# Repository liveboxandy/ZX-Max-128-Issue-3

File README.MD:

ZX Max 128 Issue 3.

This Kicad project has only been done so as to allow for a proper ibom that includes tracks and vias
to be created to make assembling easier.
A lot of work was done in order to ensure that the footprints were located as close as possible to 
those in the original as well tying to follow the existing track and via locations. Some of the
footprints that were downloaded from Digikey based on the parts in the official BOM do not fit 
exactly in their locations on the board. C15 is one example, I had to modify it's footprint to fit
the pad dimensions. Some other capacitors also do not fit correctly but appear to be close enough.

As such, although I have tried to be as accurate as possible I would NOT use these gerbers to have a
pcb manufactured without having another set of eyes checking that the schematic that I have produced
is correct to that produced by DonSuperfo and that the pcb data from Kicad reports no major errors 
with regards to copper tracing and via positions.

The KiCAD schematics 'should' be correct but nothing should be assumed as correct without checking with the original schematic and PCB layout. Although I have followed the original track and via layout further checking should be done before using these files to order a pcb with. Currently I would still order the pcb from PCBWay using the link from https://github.com/DonSuperfo/ZX-Max-128

Note that any part number for any device used in this project might not be the correct one from the original BOM as supplied from PCBWay as I had to change some parts to get a footprint that would fit in the space on the original pcb with the correct pin spacing. This required selecting a different part number or vendor. This applies mainly to capacitors. Some other parts are no longer available under that number from Digikey.

As always, measure twice and order one.

Use at your own risk.

For the jumpers/connectors on the board,

J1/J1A1 8 Way Keyboard Connector

J2/J2A1 5 Way Keyboard Connector

J3 Zx Expansion Connector

J4 DC Input can be any polarity. 

J5 Video is a TRRS, Tip-Video,RR-Left/Right, Screen-Ground.

J6 Ear/Mic. Wired as per ZX Spectrum 128K +3. TRS. Tip-Mic, Ring-Ear, Screen-Ground.

J7 Not Used

J8 SCART, mates with a Sega megadrive cable for SCART.

J9 Not Used

J10 EEPROM/EPROM selection, EEPROM 2-4/1-3, UVEPROM 2-1/4-3.

J11 Speaker On/Off

J12 Not Used

J13 Not Used

J14 JTAG for the EPM7128 wired as standard to an Altera device.

J15 Not Used

J16 Disable DivMMC, close = enable DivMMC, open = disable DivMMC or need to update program on U17

SW1 RESET

From information on the original website,

In order to make ACB output more balanced I would recommend following the -4.5 dB panning law rule and make these updates:

R54, R55 = 470 Ohm
R51, R52 = 560 Ohm
R50, R53 = 330 Ohm

The ratio of 560 / 330 = 1.6969 is a close approximation of 1 / 10^(-4.5 / 20) = 1.6788. 
Also the resulting equivalent resistance is around 1000 Ohm which leads to less distortion on AY outputs.

mismatch between the value on the scheme and in the BOM for part R32 (INT)
on scheme it is 470R but in BOM 10k.
it looks like in BOM incorrect value.

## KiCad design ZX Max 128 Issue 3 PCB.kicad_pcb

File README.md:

# ZX-Max-128-Issue-3
KiCAD created files for the ZX Max 128 Issue 3 designed by DonSuperfo

This Kicad project has only been done so as to allow for a proper ibom that includes tracks and vias
to be created.
A lot of work was done in order to ensure that the footprints were located as close as possible to 
those in the original as well tying to follow the existing track and via locations. Some of the
footprints that were downloaded from Digikey based on the parts in the official BOM do not fit 
exactly in their locations on the board. C15 is one example, I had to modify it's footprint to fit
the pad dimensions. Some other capacitors also do not fit correctly but appear to be close enough.

As such, although I have tried to be as accurate as possible I would NOT use these gerbers to have a
pcb manufactured without having another set of eyes checking that the schematic that I have produced
is correct to that produced by DonSuperfo and that the pcb data from Kicad reports no major errors 
with regards to copper tracing and via positions.

For the jumpers/connectors on the board,

J1 8 Way Keyboard Connector
J2 5 Way Keyboard Connector
J3 Zx Expansion Connector
J4 DC Input can be any polarity. 
J5 Video is a TRRS, Tip-Video,RR-Left/Right, Screen-Ground.
J6 Ear/Mic. Wired as per ZX Spectrum 128K +3. TRS. Tip-Mic, Ring-Ear, Screen-Ground.
J7 Not Used
J8 SCART, mates with a Sega megadrive cable for SCART.
J9 Not Used
J10 EPROM/EEPROM selection,
J11 Speaker On/Off
J12 Not Used
J13 Not Used
J14 JTAG for the EPM7128 wired as standard to an Altera device.
J15 Not Used
J16 Disable DivMMC, close = enable DivMMC, open = disable DivMMC or need to update program on U17
SW1 RESET

From information on the original website,

In order to make ACB output more balanced I would recommend following the -4.5 dB panning law rule and make these updates:

R54, R55 = 470 Ohm
R51, R52 = 560 Ohm
R50, R53 = 330 Ohm

The ratio of 560 / 330 = 1.6969 is a close approximation of 1 / 10^(-4.5 / 20) = 1.6788. 
Also the resulting equivalent resistance is around 1000 Ohm which leads to less distortion on AY outputs.

mismatch between the value on the scheme and in the BOM for part R32 (INT)
on scheme it is 470R but in BOM 10k.
it looks like in BOM incorrect value.

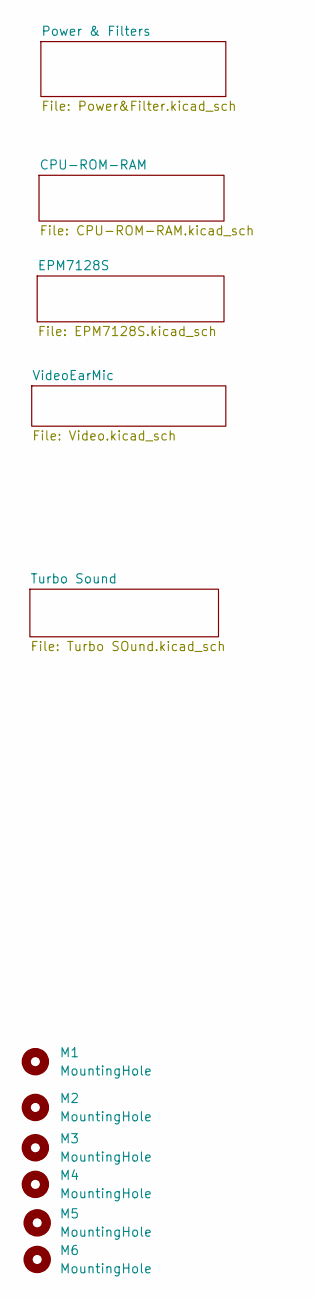
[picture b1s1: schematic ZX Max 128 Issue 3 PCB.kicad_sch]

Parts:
M1, M2, M3, M4, M5, M6: MountingHole; MountingHole_3.2mm_M3_DIN965

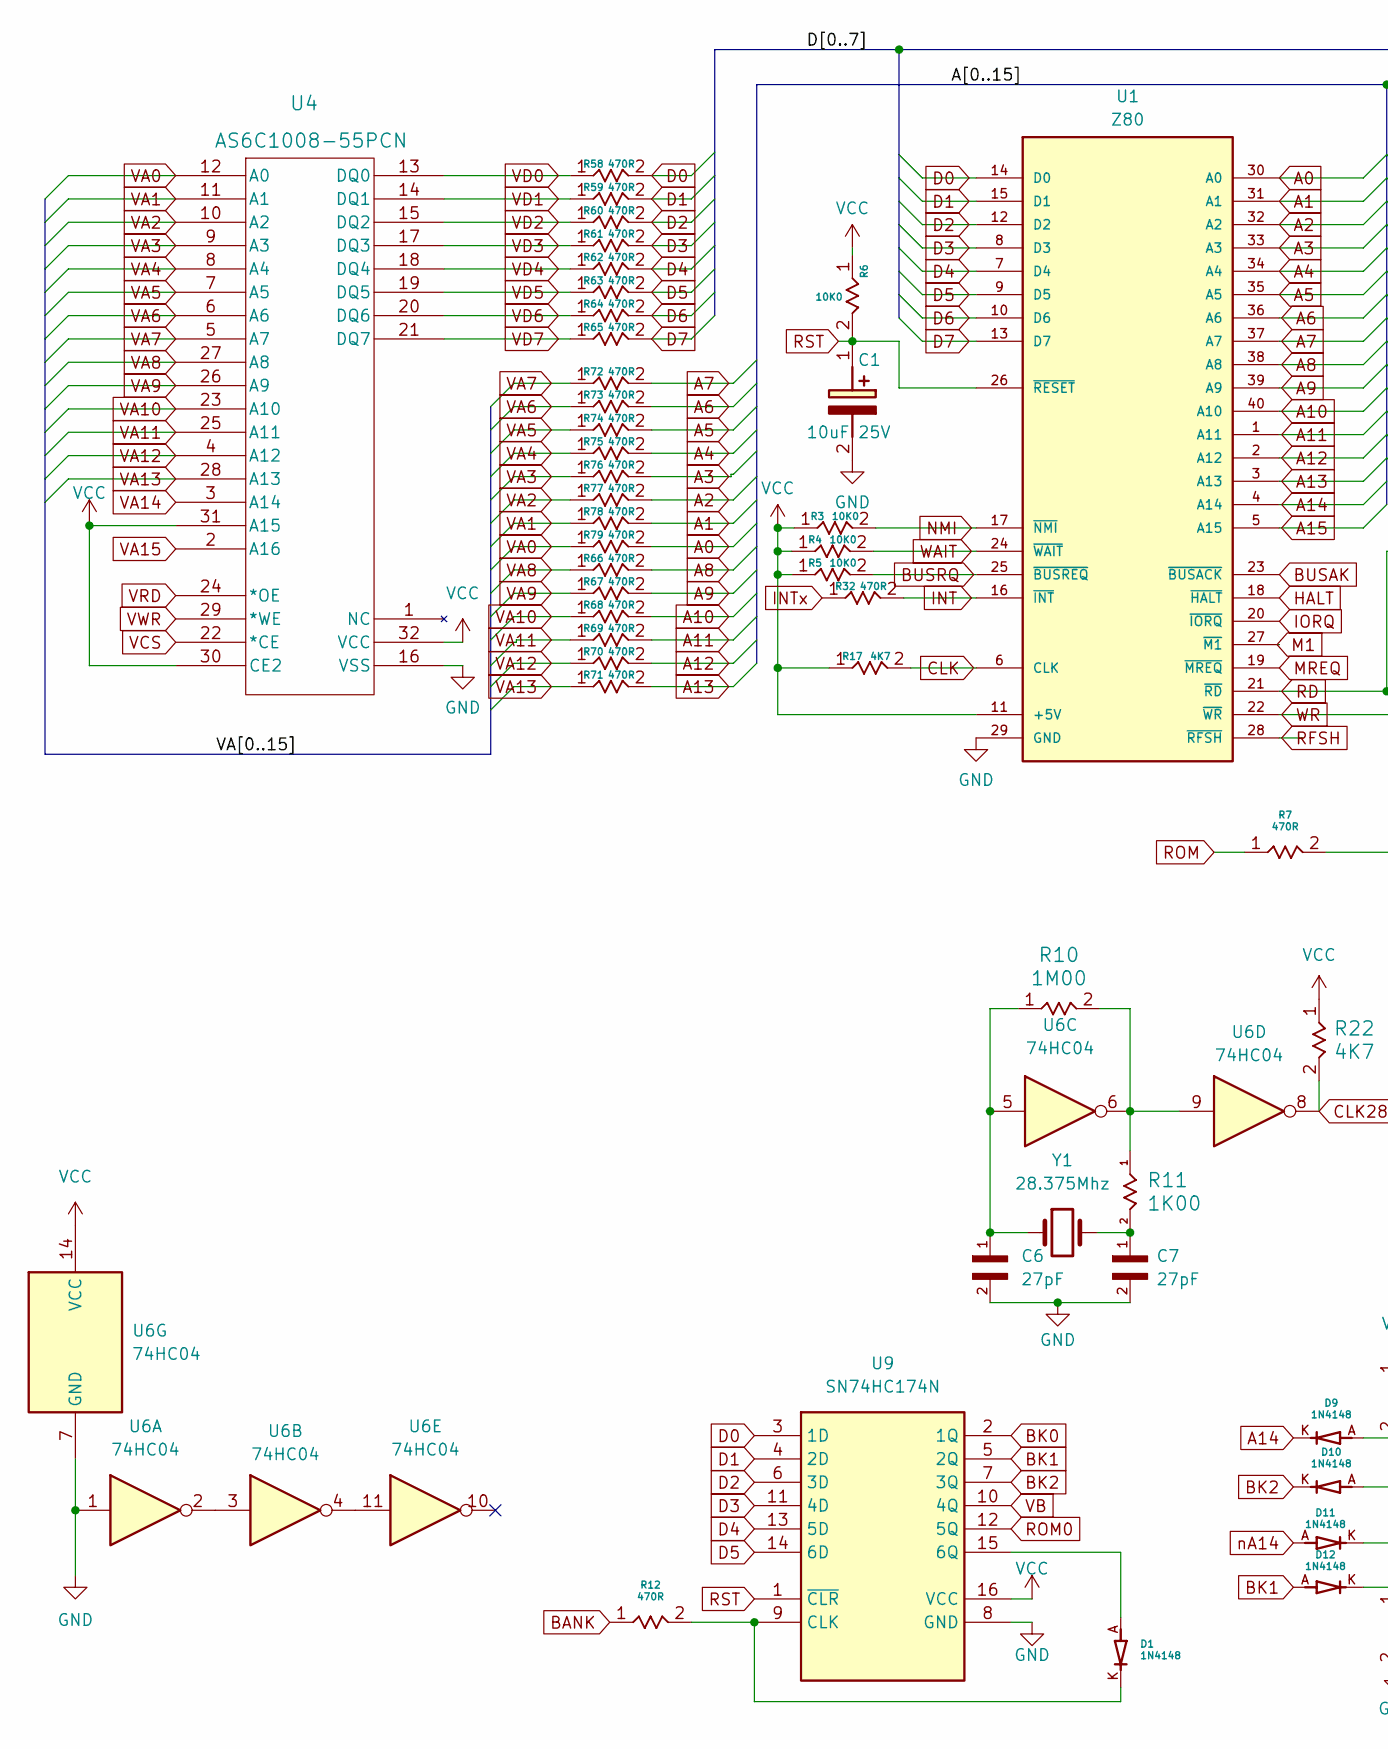
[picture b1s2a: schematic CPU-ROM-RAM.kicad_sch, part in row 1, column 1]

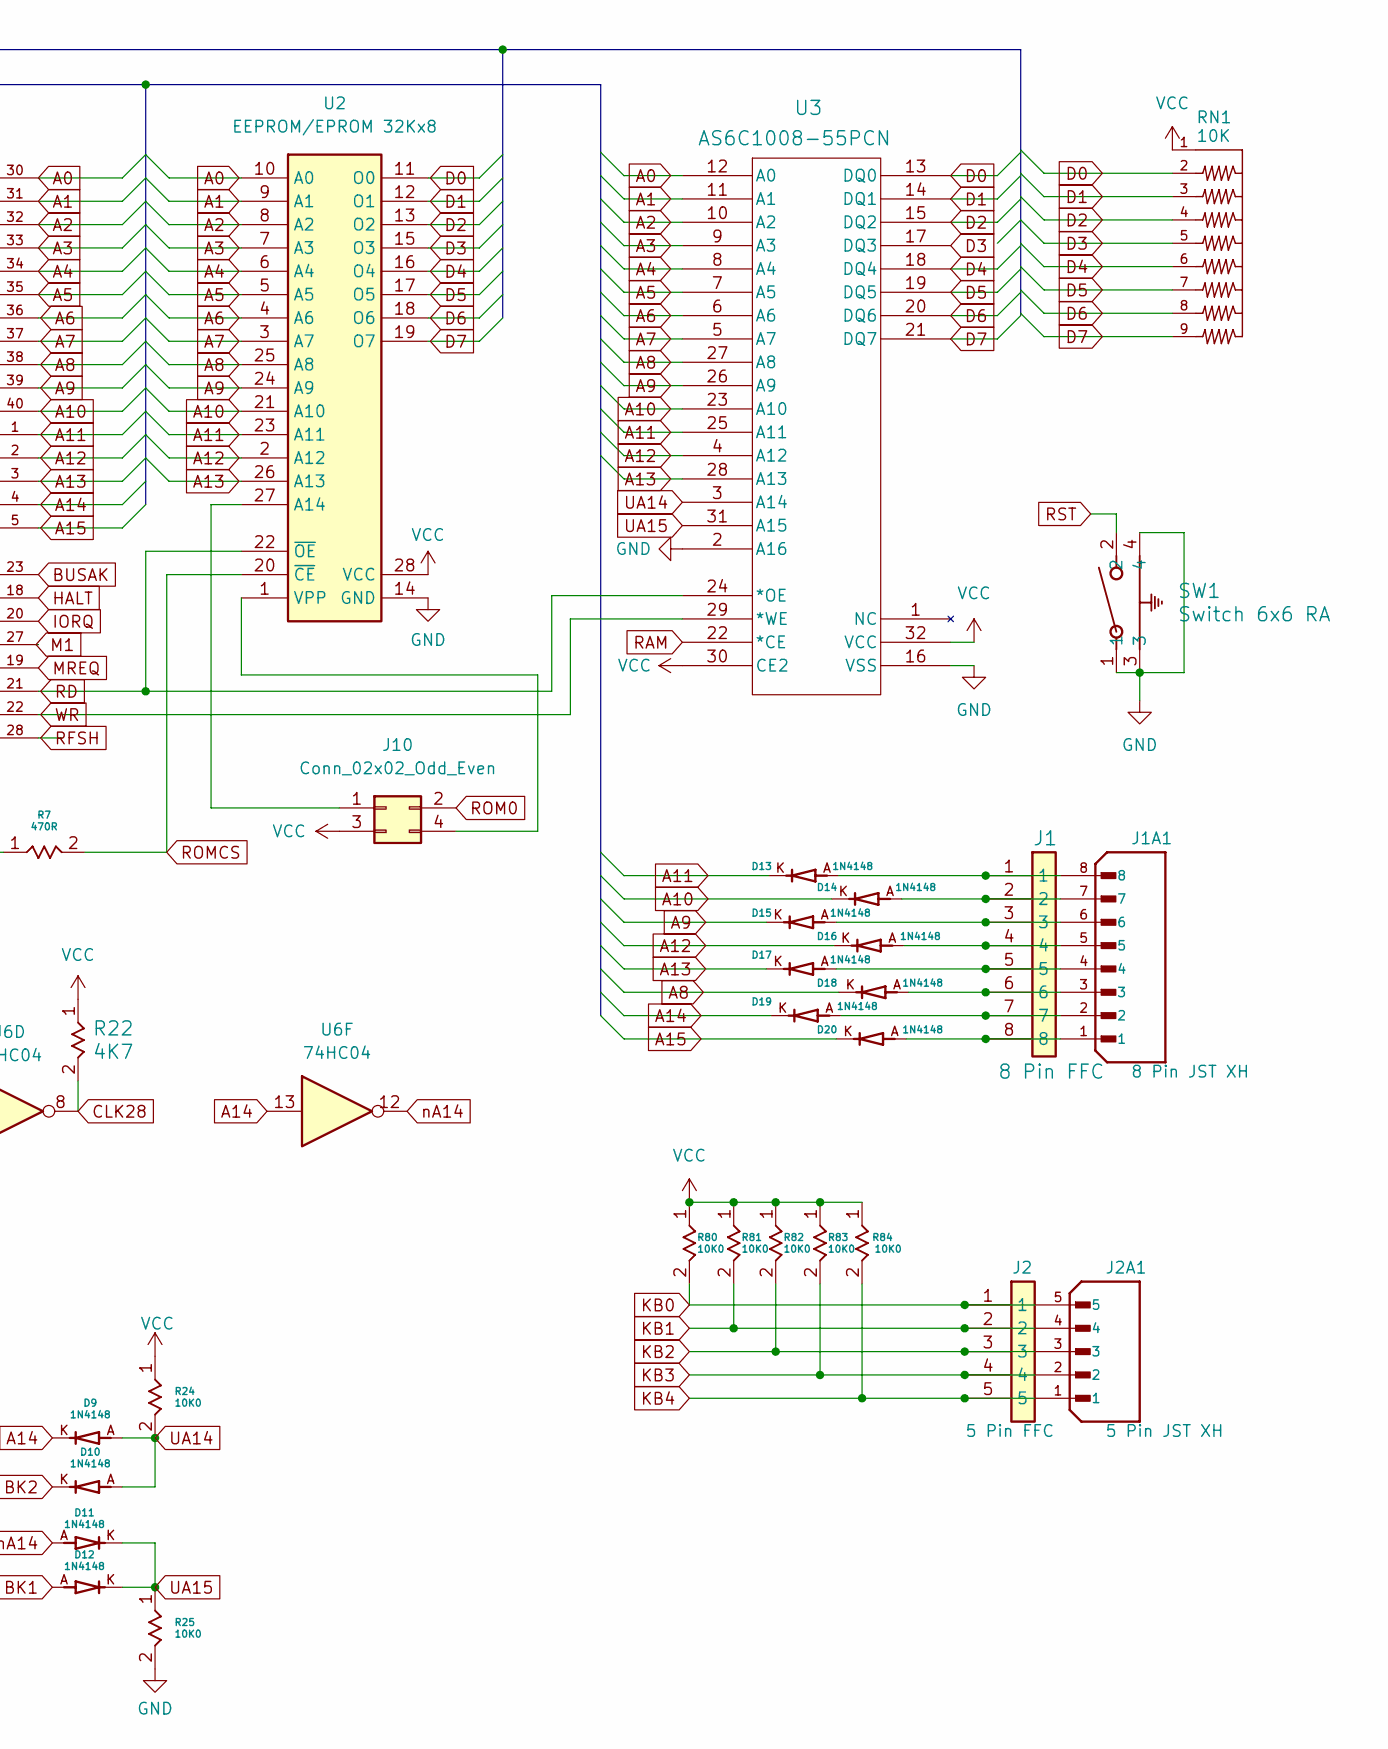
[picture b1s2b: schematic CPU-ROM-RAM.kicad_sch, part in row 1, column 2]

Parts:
C1: 10uF 25V; CAPPRD200W50D500H1100; Mouser Part Number 667-ECA-1EM100B
C6, C7: 27pF; CAPRB250W50L400T250H550; PARTREV 20200310
D1, D9, D10, D11, D12, D13, D14, D15, D16, D17, D18, D19, D20: 1N4148; DIOAD753W49L380D172B; PARTREV 5
J1: 8 Pin FFC; 55203155
J1A1: 8 Pin JST XH; JST_B8B-XH-A_LF__SN_; PARTREV 7/4/21
J2: 5 Pin FFC; 55203155; Mouser Part Number 571-5-520315-5
J2A1: 5 Pin JST XH; JST_B5B-XH-A_LF__SN_; PARTREV 7/4/21
J10: Conn_02x02_Odd_Even; PinHeader_2x02_P2.54mm_Vertical
R3, R4, R5, R6, R24, R25, R80, R81, R82, R83, R84: 10K0; STA_CF14_STP
R7, R12, R32, R58, R59, R60, R61, R62, R63, R64, R65, R66, R67, R68, R69, R70, R71, R72, R73, R74, R75, R76, R77, R78, R79: 470R; STA_CF14_STP
R10: 1M00; STA_CF14_STP
R11: 1K00; STA_CF14_STP
R17, R22: 4K7; STA_CF14_STP
RN1: 10K; SIP249W50P254L2281H508Q9; PARTREV 10/1/20
SW1: Switch 6x6 RA; SW2_1825027-G_TEC
U1: Z80; Z80_Socket
U2: EEPROM/EPROM 32Kx8; DIP1556W56P254L3702H483Q28N; Mouser Part Number 556-AT27C256R-45PU
U3: AS6C1008-55PCN; U3
U4: AS6C1008-55PCN; PDIP-32_MIL600_ALL
U6: 74HC04; DIP794W53P254L1930H508Q14N
U9: SN74HC174N; DIP794W53P254L1930H508Q16N; Mouser Part Number 595-SN74HC174N
Y1: 28.375Mhz; Crystal_HC49-4H_Vertical

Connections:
A0: R79.2, U1.30 (A0), U2.10 (A0), U3.12 (A0); also elsewhere on the board
A1: R78.2, U1.31 (A1), U2.9 (A1), U3.11 (A1); also elsewhere on the board
A2: R77.2, U1.32 (A2), U2.8 (A2), U3.10 (A2); also elsewhere on the board
A3: R76.2, U1.33 (A3), U2.7 (A3), U3.9 (A3); also elsewhere on the board
A4: R75.2, U1.34 (A4), U2.6 (A4), U3.8 (A4); also elsewhere on the board
A5: R74.2, U1.35 (A5), U2.5 (A5), U3.7 (A5); also elsewhere on the board
A6: R73.2, U1.36 (A6), U2.4 (A6), U3.6 (A6); also elsewhere on the board
A7: R72.2, U1.37 (A7), U2.3 (A7), U3.5 (A7); also elsewhere on the board
A8: D18.K, R66.2, U1.38 (A8), U2.25 (A8), U3.27 (A8); also elsewhere on the board
A9: D15.K, R67.2, U1.39 (A9), U2.24 (A9), U3.26 (A9); also elsewhere on the board
A10: D14.K, R68.2, U1.40 (A10), U2.21 (A10), U3.23 (A10); also elsewhere on the board
A11: D13.K, R69.2, U1.1 (A11), U2.23 (A11), U3.25 (A11); also elsewhere on the board
A12: D16.K, R70.2, U1.2 (A12), U2.2 (A12), U3.4 (A12); also elsewhere on the board
A13: D17.K, R71.2, U1.3 (A13), U2.26 (A13), U3.28 (A13); also elsewhere on the board
A14: D9.K, D19.K, U1.4 (A14), U6.13; also elsewhere on the board
A15: D20.K, U1.5 (A15); also elsewhere on the board
BANK: R12.1; also elsewhere on the board
BK0: U9.2 (1Q); also elsewhere on the board
BK1: D12.A, U9.5 (2Q); also elsewhere on the board
BK2: D10.K, U9.7 (3Q); also elsewhere on the board
BUSAK: U1.23 (~BUSACK); also elsewhere on the board
BUSRQ: R5.2, U1.25 (~BUSREQ); also elsewhere on the board
CLK: R17.2, U1.6 (CLK); also elsewhere on the board
CLK28: R22.2, U6.8; also elsewhere on the board
D0: R58.2, RN1.2, U1.14 (D0), U2.11 (O0), U3.13 (DQ0), U9.3 (1D); also elsewhere on the board
D1: R59.2, RN1.3, U1.15 (D1), U2.12 (O1), U3.14 (DQ1), U9.4 (2D); also elsewhere on the board
D2: R60.2, RN1.4, U1.12 (D2), U2.13 (O2), U3.15 (DQ2), U9.6 (3D); also elsewhere on the board
D3: R61.2, RN1.5, U1.8 (D3), U2.15 (O3), U3.17 (DQ3), U9.11 (4D); also elsewhere on the board
D4: R62.2, RN1.6, U1.7 (D4), U2.16 (O4), U3.18 (DQ4), U9.13 (5D); also elsewhere on the board
D5: R63.2, RN1.7, U1.9 (D5), U2.17 (O5), U3.19 (DQ5), U9.14 (6D); also elsewhere on the board
D6: R64.2, RN1.8, U1.10 (D6), U2.18 (O6), U3.20 (DQ6); also elsewhere on the board
D7: R65.2, RN1.9, U1.13 (D7), U2.19 (O7), U3.21 (DQ7); also elsewhere on the board
GND: C1.2 (-), C6.2, C7.2, R25.2, SW1.1, SW1.3, SW1.4, U1.29 (GND), U2.14 (GND), U3.2 (A16), U3.16 (VSS), U4.16 (VSS), U6.1, U6.7 (GND), U9.8 (GND); also elsewhere on the board
HALT: U1.18 (~HALT); also elsewhere on the board
INT: R32.2, U1.16 (~INT); also elsewhere on the board
INTx: R32.1; also elsewhere on the board
IORQ: U1.20 (~IORQ); also elsewhere on the board
KB0: J2.1, J2A1.5, R80.2; also elsewhere on the board
KB1: J2.2, J2A1.4, R81.2; also elsewhere on the board
KB2: J2.3, J2A1.3, R82.2; also elsewhere on the board
KB3: J2.4, J2A1.2, R83.2; also elsewhere on the board
KB4: J2.5, J2A1.1, R84.2; also elsewhere on the board
M1: U1.27 (~M1); also elsewhere on the board
MREQ: U1.19 (~MREQ); also elsewhere on the board
NMI: R3.2, U1.17 (~NMI); also elsewhere on the board
unnamed: C6.1, R10.1, U6.5, Y1.1
unnamed: C7.1, R11.2, Y1.2
unnamed: D13.A, J1.1, J1A1.8
unnamed: D14.A, J1.2, J1A1.7
unnamed: D15.A, J1.3, J1A1.6
unnamed: D16.A, J1.4, J1A1.5
unnamed: D17.A, J1.5, J1A1.4
unnamed: D18.A, J1.6, J1A1.3
unnamed: D19.A, J1.7, J1A1.2
unnamed: D20.A, J1.8, J1A1.1
unnamed: J10.1, U2.27 (A14)
unnamed: J10.4, U2.1 (VPP)
unnamed: R10.2, R11.1, U6.6, U6.9
unnamed: U6.2, U6.3
unnamed: U6.4, U6.11
unnamed: D1.A, U9.15 (6Q)
unnamed: D1.K, R12.2, U9.9 (CLK)
RAM: U3.22 (*CE); also elsewhere on the board
RD: U1.21 (~RD), U2.22 (~OE), U3.24 (*OE); also elsewhere on the board
RFSH: U1.28 (~RFSH); also elsewhere on the board
ROM: R7.1; also elsewhere on the board
ROM0: J10.2, U9.12 (5Q)
ROMCS: R7.2, U2.20 (~CE); also elsewhere on the board
RST: C1.1 (+), R6.2, SW1.2, U1.26 (~RESET), U9.1 (~CLR); also elsewhere on the board
UA14: D9.A, D10.A, R24.2, U3.3 (A14)
UA15: D11.K, D12.K, R25.1, U3.31 (A15)
VA0: R79.1, U4.12 (A0); also elsewhere on the board
VA1: R78.1, U4.11 (A1); also elsewhere on the board
VA2: R77.1, U4.10 (A2); also elsewhere on the board
VA3: R76.1, U4.9 (A3); also elsewhere on the board
VA4: R75.1, U4.8 (A4); also elsewhere on the board
VA5: R74.1, U4.7 (A5); also elsewhere on the board
VA6: R73.1, U4.6 (A6); also elsewhere on the board
VA7: R72.1, U4.5 (A7); also elsewhere on the board
VA8: R66.1, U4.27 (A8); also elsewhere on the board
VA9: R67.1, U4.26 (A9); also elsewhere on the board
VA10: R68.1, U4.23 (A10); also elsewhere on the board
VA11: R69.1, U4.25 (A11); also elsewhere on the board
VA12: R70.1, U4.4 (A12); also elsewhere on the board
VA13: R71.1, U4.28 (A13); also elsewhere on the board
VA14: U4.3 (A14); also elsewhere on the board
VA15: U4.2 (A16); also elsewhere on the board
VB: U9.10 (4Q); also elsewhere on the board
VCC: J10.3, R3.1, R4.1, R5.1, R6.1, R17.1, R22.1, R24.1, R80.1, R81.1, R82.1, R83.1, R84.1, RN1.1, U1.11 (+5V), U2.28 (VCC), U3.30 (CE2), U3.32 (VCC), U4.30 (CE2), U4.31 (A15), U4.32 (VCC), U6.14 (VCC), U9.16 (VCC); also elsewhere on the board
VCS: U4.22 (*CE); also elsewhere on the board
VD0: R58.1, U4.13 (DQ0); also elsewhere on the board
VD1: R59.1, U4.14 (DQ1); also elsewhere on the board
VD2: R60.1, U4.15 (DQ2); also elsewhere on the board
VD3: R61.1, U4.17 (DQ3); also elsewhere on the board
VD4: R62.1, U4.18 (DQ4); also elsewhere on the board
VD5: R63.1, U4.19 (DQ5); also elsewhere on the board
VD6: R64.1, U4.20 (DQ6); also elsewhere on the board
VD7: R65.1, U4.21 (DQ7); also elsewhere on the board
VRD: U4.24 (*OE); also elsewhere on the board
VWR: U4.29 (*WE); also elsewhere on the board
WAIT: R4.2, U1.24 (~WAIT); also elsewhere on the board
WR: U1.22 (~WR), U3.29 (*WE); also elsewhere on the board
nA14: D11.A, U6.12

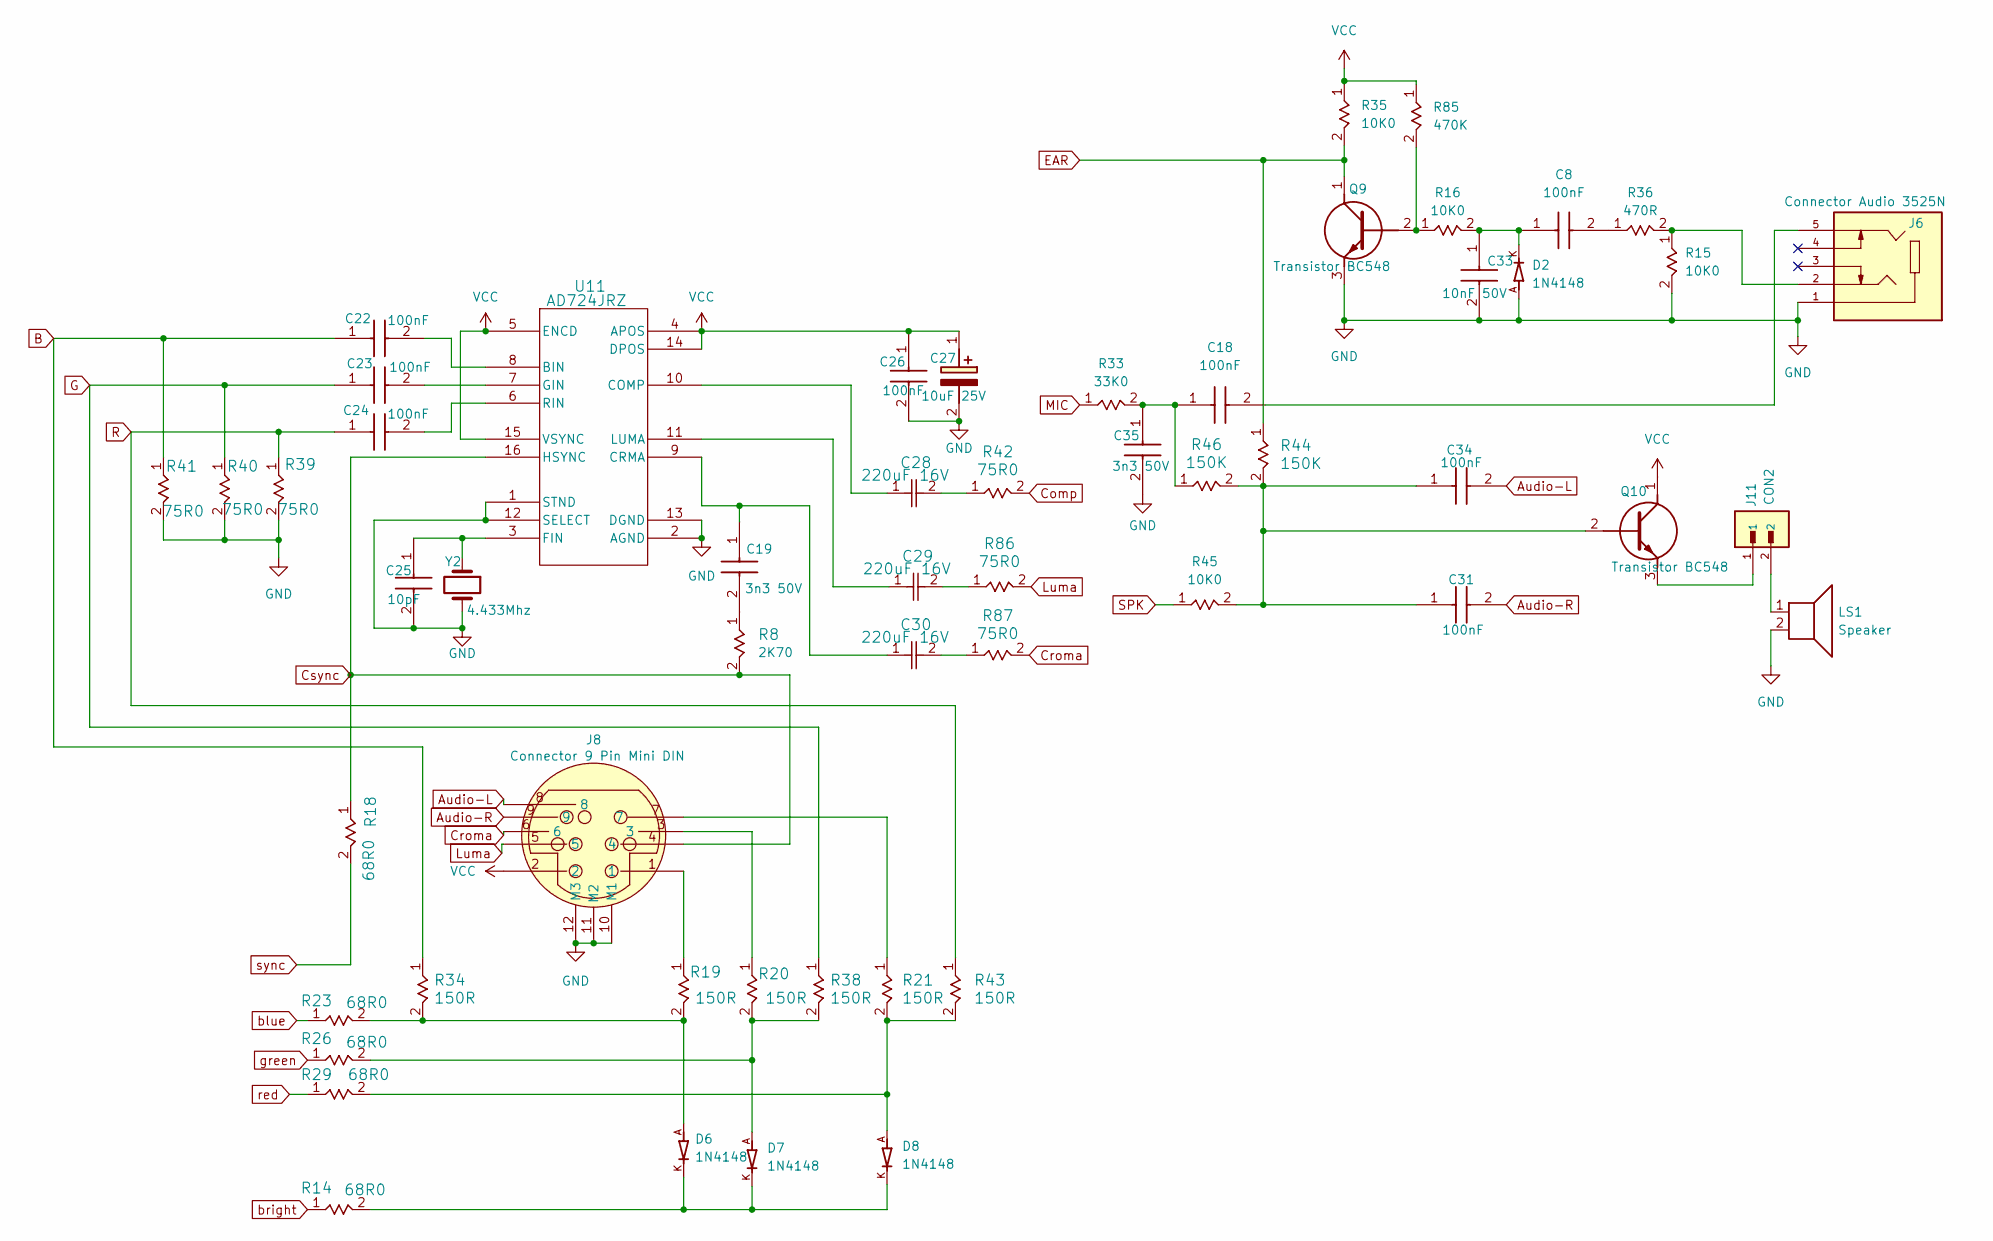
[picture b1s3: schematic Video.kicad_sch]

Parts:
C8, C18, C22, C23, C24, C26, C31, C34: 100nF; CAPRB250W50L400T250H550; Mouser Part Number 594-K104Z15Y5VF5TL2
C19, C35: 3n3 50V; CAPRB250W50L400T250H550; Mouser Part Number 594-K104Z15Y5VF5TL2
C25: 10pF; CAPRB250W50L400T250H550; Mouser Part Number 594-K104Z15Y5VF5TL2
C27: 10uF 25V; CAPPRD200W50D500H1100; Mouser Part Number 667-ECA-1EM100B
C28, C29, C30: 220uF 16V; CAP_YX_6P3X11_RUB
C33: 10nF 50V; CAPRB250W50L400T250H550; Mouser Part Number 594-K104Z15Y5VF5TL2
D2, D6, D7, D8: 1N4148; DIOAD753W49L380D172B; PARTREV 5
J6: Connector Audio 3525N; CUI_SJ1-3525N
J8: Connector 9 Pin Mini DIN; KMDGX9SBS1
J11: CON2; HARWIN_M20-9990246; PARTREV 14
LS1: Speaker
Q9, Q10: Transistor BC548; BC548BTA
R8: 2K70; STA_CF14_STP
R14, R18, R23, R26, R29: 68R0; STA_CF14_STP
R15, R16, R35, R45: 10K0; STA_CF14_STP
R19, R20, R21, R34, R38, R43: 150R; STA_CF14_STP
R33: 33K0; STA_CF14_STP
R36: 470R; STA_CF14_STP
R39, R40, R41, R42, R86, R87: 75R0; STA_CF14_STP
R44, R46: 150K; STA_CF14_STP
R85: 470K; STA_CF14_STP
U11: AD724JRZ; RW_16_ADI
Y2: 4.433Mhz; Crystal_HC49-4H_Vertical

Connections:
Audio-L: C34.2 (-), J8.8; also elsewhere on the board
Audio-R: C31.2 (-), J8.9; also elsewhere on the board
B: C22.1 (+), R34.1, R41.1
Comp: R42.2; also elsewhere on the board
Croma: J8.6, R87.2
Csync: J8.4, R8.2, R18.1, U11.16 (HSYNC)
EAR: Q9.1 (C), R35.2, R44.1; also elsewhere on the board
G: C23.1 (+), R38.1, R40.1
GND: C25.2 (-), C26.2 (-), C27.2 (-), C33.2 (-), C35.2 (-), D2.A, J6.1, J8.10 (M1), J8.11 (M2), J8.12 (M3), LS1.2, Q9.3 (E), R15.2, R39.2, R40.2, R41.2, U11.1 (STND), U11.2 (AGND), U11.12 (SELECT), U11.13 (DGND), Y2.2; also elsewhere on the board
Luma: J8.5, R86.2
MIC: R33.1; also elsewhere on the board
unnamed: C8.2 (-), R36.1
unnamed: C18.1 (+), C35.1 (+), R33.2, R46.1
unnamed: C18.2 (-), J6.5
unnamed: C19.1 (+), C30.1, U11.9 (CRMA)
unnamed: C19.2 (-), R8.1
unnamed: C22.2 (-), U11.8 (BIN)
unnamed: C23.2 (-), U11.7 (GIN)
unnamed: C24.2 (-), U11.6 (RIN)
unnamed: C25.1 (+), U11.3 (FIN), Y2.1
unnamed: C28.2, R42.1
unnamed: C29.2, R86.1
unnamed: C30.2, R87.1
unnamed: C31.1 (+), C34.1 (+), Q10.2 (B), R44.2, R45.2, R46.2
unnamed: C8.1 (+), C33.1 (+), D2.K, R16.2
unnamed: D6.A, R19.2, R23.2, R34.2
unnamed: D6.K, D7.K, D8.K, R14.2
unnamed: D7.A, R20.2, R26.2, R38.2
unnamed: D8.A, R21.2, R29.2, R43.2
unnamed: J6.2, R15.1, R36.2
unnamed: J8.1, R19.1
unnamed: J8.3, R20.1
unnamed: J8.7, R21.1
unnamed: J11.2, LS1.1
unnamed: Q9.2 (B), R16.1, R85.2
unnamed: J11.1, Q10.3 (E)
unnamed: C28.1, U11.10 (COMP)
unnamed: C29.1, U11.11 (LUMA)
R: C24.1 (+), R39.1, R43.1
SPK: R45.1; also elsewhere on the board
VCC: C26.1 (+), C27.1 (+), J8.2, Q10.1 (C), R35.1, R85.1, U11.4 (APOS), U11.5 (ENCD), U11.14 (DPOS), U11.15 (VSYNC); also elsewhere on the board
blue: R23.1; also elsewhere on the board
bright: R14.1; also elsewhere on the board
green: R26.1; also elsewhere on the board
red: R29.1; also elsewhere on the board
sync: R18.2; also elsewhere on the board

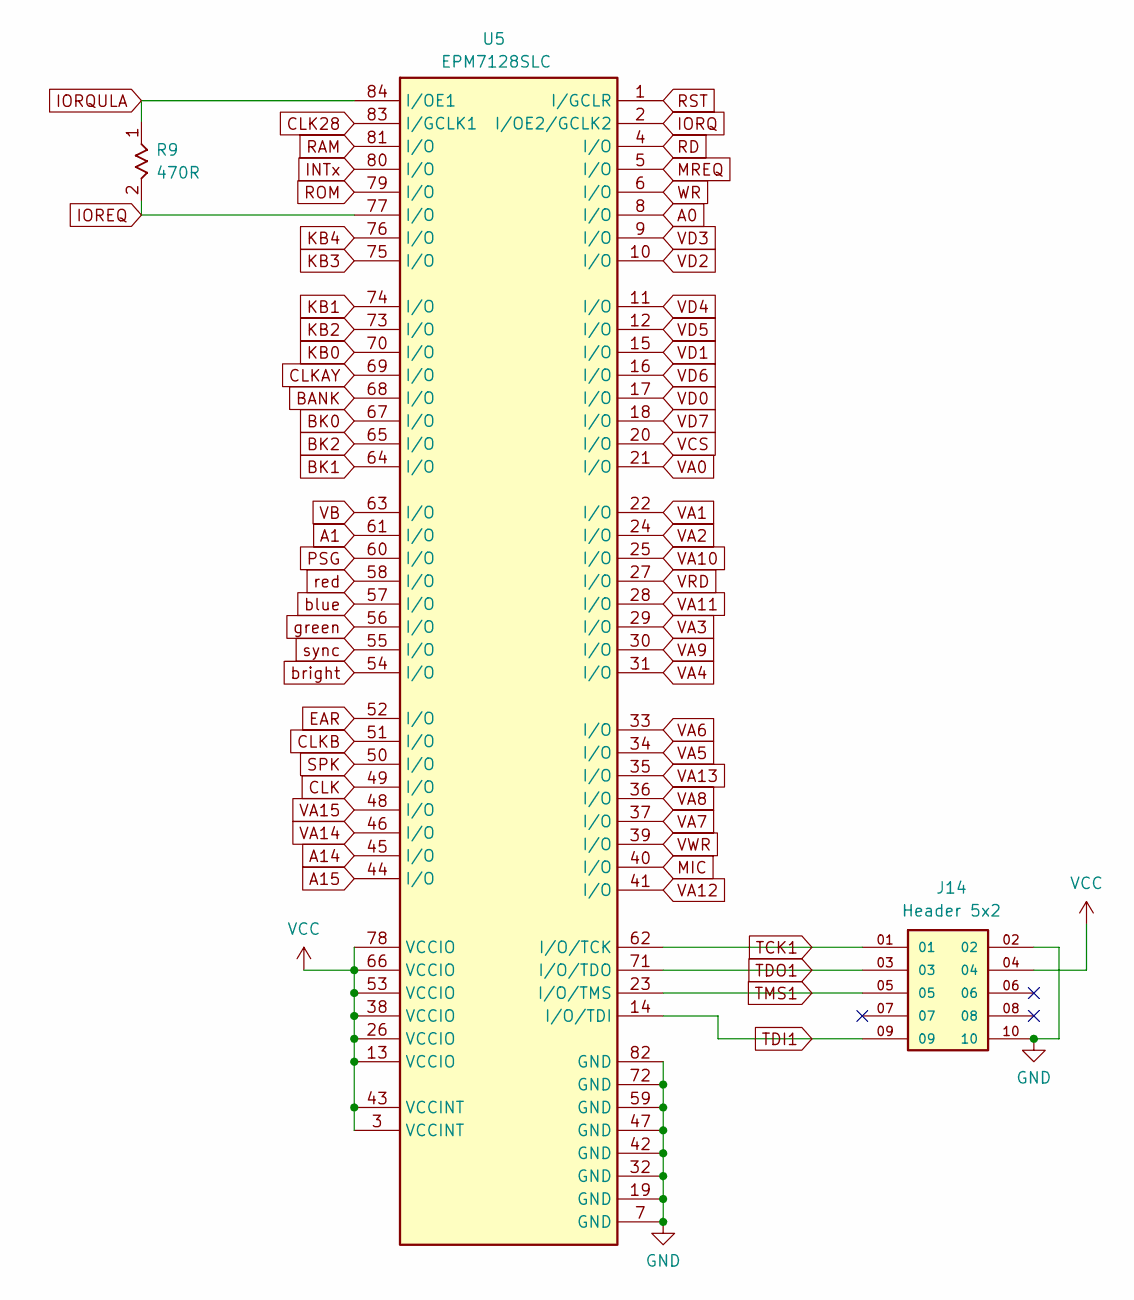
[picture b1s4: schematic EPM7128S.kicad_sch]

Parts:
J14: Header 5x2; AMPHENOL_10129381-910002BLF; PARTREV D
R9: 470R; STA_CF14_STP
U5: EPM7128SLC; PLCC84AT

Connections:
A0: U5.8 (I/O); also elsewhere on the board
A1: U5.61 (I/O); also elsewhere on the board
A14: U5.45 (I/O); also elsewhere on the board
A15: U5.44 (I/O); also elsewhere on the board
BANK: U5.68 (I/O); also elsewhere on the board
BK0: U5.67 (I/O); also elsewhere on the board
BK1: U5.64 (I/O); also elsewhere on the board
BK2: U5.65 (I/O); also elsewhere on the board
CLK: U5.49 (I/O); also elsewhere on the board
CLK28: U5.83 (I/GCLK1); also elsewhere on the board
CLKAY: U5.69 (I/O); also elsewhere on the board
CLKB: U5.51 (I/O); also elsewhere on the board
EAR: U5.52 (I/O); also elsewhere on the board
GND: J14.02, J14.10, U5.7 (GND), U5.19 (GND), U5.32 (GND), U5.42 (GND), U5.47 (GND), U5.59 (GND), U5.72 (GND), U5.82 (GND); also elsewhere on the board
INTx: U5.80 (I/O); also elsewhere on the board
IOREQ: R9.2, U5.77 (I/O)
IORQ: U5.2 (I/OE2/GCLK2); also elsewhere on the board
IORQULA: R9.1, U5.84 (I/OE1); also elsewhere on the board
KB0: U5.70 (I/O); also elsewhere on the board
KB1: U5.74 (I/O); also elsewhere on the board
KB2: U5.73 (I/O); also elsewhere on the board
KB3: U5.75 (I/O); also elsewhere on the board
KB4: U5.76 (I/O); also elsewhere on the board
MIC: U5.40 (I/O); also elsewhere on the board
MREQ: U5.5 (I/O); also elsewhere on the board
PSG: U5.60 (I/O); also elsewhere on the board
RAM: U5.81 (I/O); also elsewhere on the board
RD: U5.4 (I/O); also elsewhere on the board
ROM: U5.79 (I/O); also elsewhere on the board
RST: U5.1 (I/GCLR); also elsewhere on the board
SPK: U5.50 (I/O); also elsewhere on the board
TCK1: J14.01, U5.62 (I/O/TCK)
TDI1: J14.09, U5.14 (I/O/TDI)
TDO1: J14.03, U5.71 (I/O/TDO)
TMS1: J14.05, U5.23 (I/O/TMS)
VA0: U5.21 (I/O); also elsewhere on the board
VA1: U5.22 (I/O); also elsewhere on the board
VA2: U5.24 (I/O); also elsewhere on the board
VA3: U5.29 (I/O); also elsewhere on the board
VA4: U5.31 (I/O); also elsewhere on the board
VA5: U5.34 (I/O); also elsewhere on the board
VA6: U5.33 (I/O); also elsewhere on the board
VA7: U5.37 (I/O); also elsewhere on the board
VA8: U5.36 (I/O); also elsewhere on the board
VA9: U5.30 (I/O); also elsewhere on the board
VA10: U5.25 (I/O); also elsewhere on the board
VA11: U5.28 (I/O); also elsewhere on the board
VA12: U5.41 (I/O); also elsewhere on the board
VA13: U5.35 (I/O); also elsewhere on the board
VA14: U5.46 (I/O); also elsewhere on the board
VA15: U5.48 (I/O); also elsewhere on the board
VB: U5.63 (I/O); also elsewhere on the board
VCC: J14.04, U5.3 (VCCINT), U5.13 (VCCIO), U5.26 (VCCIO), U5.38 (VCCIO), U5.43 (VCCINT), U5.53 (VCCIO), U5.66 (VCCIO), U5.78 (VCCIO); also elsewhere on the board
VCS: U5.20 (I/O); also elsewhere on the board
VD0: U5.17 (I/O); also elsewhere on the board
VD1: U5.15 (I/O); also elsewhere on the board
VD2: U5.10 (I/O); also elsewhere on the board
VD3: U5.9 (I/O); also elsewhere on the board
VD4: U5.11 (I/O); also elsewhere on the board
VD5: U5.12 (I/O); also elsewhere on the board
VD6: U5.16 (I/O); also elsewhere on the board
VD7: U5.18 (I/O); also elsewhere on the board
VRD: U5.27 (I/O); also elsewhere on the board
VWR: U5.39 (I/O); also elsewhere on the board
WR: U5.6 (I/O); also elsewhere on the board
blue: U5.57 (I/O); also elsewhere on the board
bright: U5.54 (I/O); also elsewhere on the board
green: U5.56 (I/O); also elsewhere on the board
red: U5.58 (I/O); also elsewhere on the board
sync: U5.55 (I/O); also elsewhere on the board

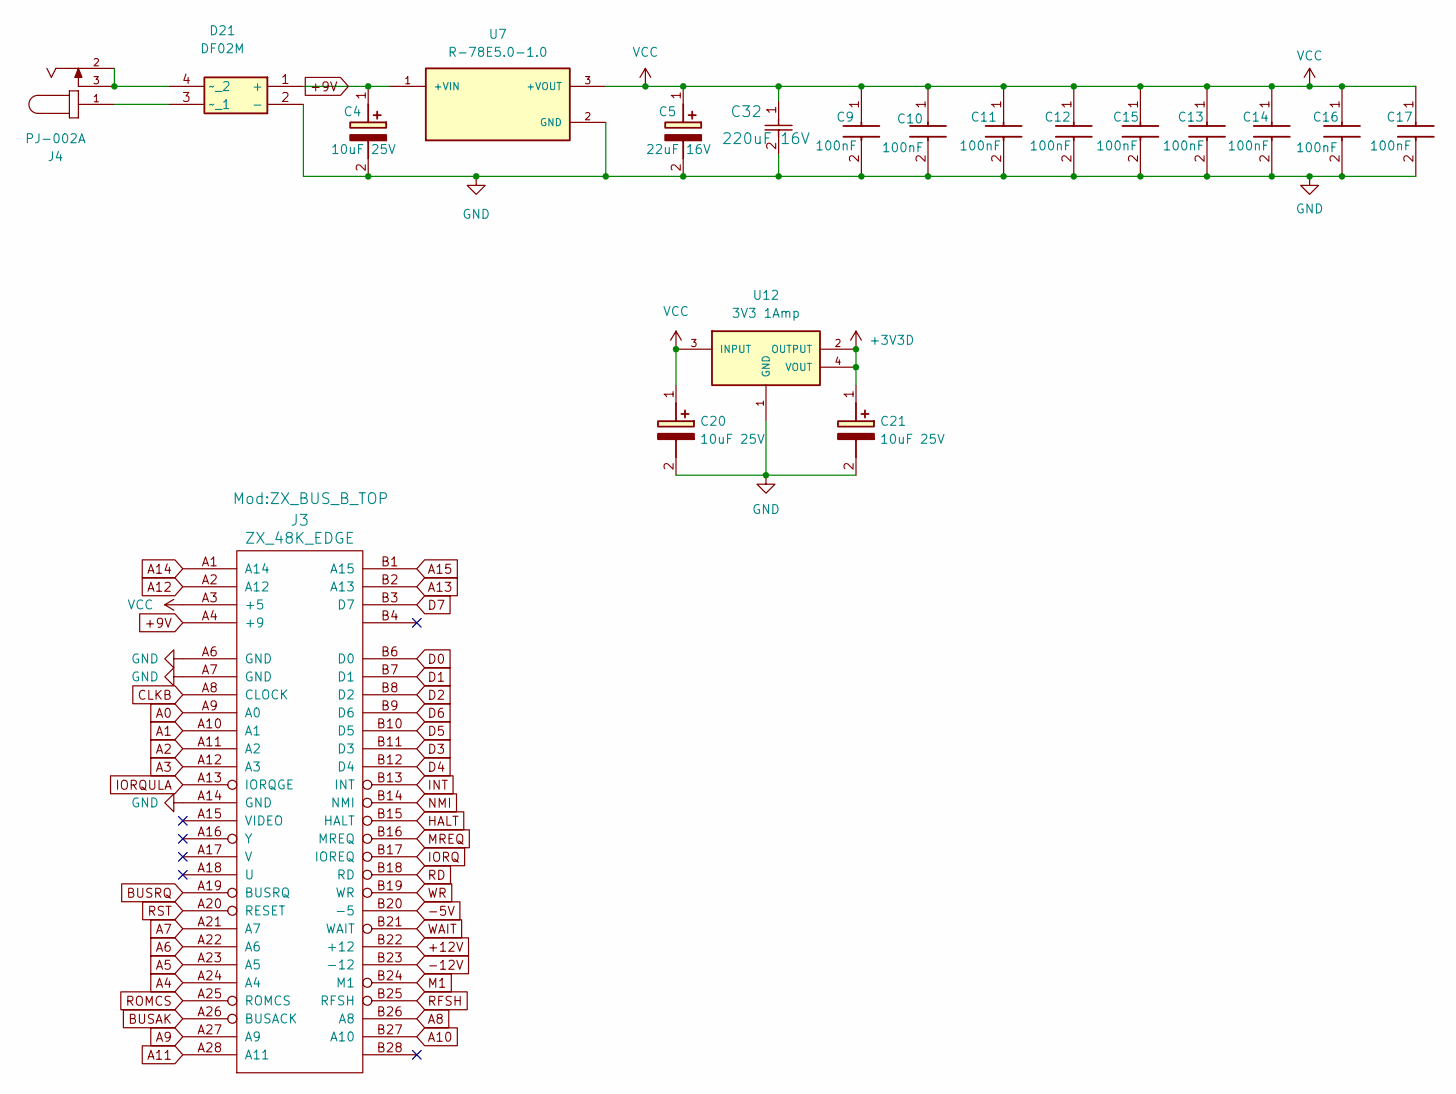
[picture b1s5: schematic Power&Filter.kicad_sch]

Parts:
C4, C20, C21: 10uF 25V; CAPPRD200W50D500H1100; Mouser Part Number 667-ECA-1EM100B
C5: 22uF 16V; CAPPRD200W50D500H1100; Mouser Part Number 667-ECA-1EM100B
C9, C10, C11, C12, C13, C14, C16, C17: 100nF; CAPRB250W50L400T250H550; Mouser Part Number 594-K104Z15Y5VF5TL2
C15: 100nF; Capacitor 3.8mm PItch; Mouser Part Number 594-K104Z15Y5VF5TL2
C32: 220uF 16V; CAP_YX_6P3X11_RUB
D21: DF02M; DIP825W58P510L832H543Q4N; Mouser Part Number 621-DF02M
J3: ZX_48K_EDGE; ZX_BUS_B_TOP
J4: PJ-002A; CUI_PJ-002A
U7: R-78E5.0-1.0; CONV_R-78E5.0-1.0; PARTREV 6
U12: 3V3 1Amp; SOT230P700X185-4N

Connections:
+3V3D: C21.1 (+), U12.2 (OUTPUT), U12.4 (VOUT); also elsewhere on the board
+9V: C4.1 (+), D21.1 (+), J3.A4 (+9), U7.1 (+VIN)
+12V: J3.B22 (+12)
-5V: J3.B20 (-5)
-12V: J3.B23 (-12)
A0: J3.A9 (A0); also elsewhere on the board
A1: J3.A10 (A1); also elsewhere on the board
A2: J3.A11 (A2); also elsewhere on the board
A3: J3.A12 (A3); also elsewhere on the board
A4: J3.A24 (A4); also elsewhere on the board
A5: J3.A23 (A5); also elsewhere on the board
A6: J3.A22 (A6); also elsewhere on the board
A7: J3.A21 (A7); also elsewhere on the board
A8: J3.B26 (A8); also elsewhere on the board
A9: J3.A27 (A9); also elsewhere on the board
A10: J3.B27 (A10); also elsewhere on the board
A11: J3.A28 (A11); also elsewhere on the board
A12: J3.A2 (A12); also elsewhere on the board
A13: J3.B2 (A13); also elsewhere on the board
A14: J3.A1 (A14); also elsewhere on the board
A15: J3.B1 (A15); also elsewhere on the board
BUSAK: J3.A26 (BUSACK); also elsewhere on the board
BUSRQ: J3.A19 (BUSRQ); also elsewhere on the board
CLKB: J3.A8 (CLOCK); also elsewhere on the board
D0: J3.B6 (D0); also elsewhere on the board
D1: J3.B7 (D1); also elsewhere on the board
D2: J3.B8 (D2); also elsewhere on the board
D3: J3.B11 (D3); also elsewhere on the board
D4: J3.B12 (D4); also elsewhere on the board
D5: J3.B10 (D5); also elsewhere on the board
D6: J3.B9 (D6); also elsewhere on the board
D7: J3.B3 (D7); also elsewhere on the board
GND: C4.2 (-), C5.2 (-), C9.2 (-), C10.2 (-), C11.2 (-), C12.2 (-), C13.2 (-), C14.2 (-), C15.2 (-), C16.2 (-), C17.2 (-), C20.2 (-), C21.2 (-), C32.2, D21.2 (-), J3.A6 (GND), J3.A7 (GND), J3.A14 (GND), U7.2 (GND), U12.1 (GND); also elsewhere on the board
HALT: J3.B15 (HALT); also elsewhere on the board
INT: J3.B13 (INT); also elsewhere on the board
IORQ: J3.B17 (IOREQ); also elsewhere on the board
IORQULA: J3.A13 (IORQGE); also elsewhere on the board
M1: J3.B24 (M1); also elsewhere on the board
MREQ: J3.B16 (MREQ); also elsewhere on the board
NMI: J3.B14 (NMI); also elsewhere on the board
unnamed: D21.3 (~_1), J4.1
unnamed: D21.4 (~_2), J4.2, J4.3
RD: J3.B18 (RD); also elsewhere on the board
RFSH: J3.B25 (RFSH); also elsewhere on the board
ROMCS: J3.A25 (ROMCS); also elsewhere on the board
RST: J3.A20 (RESET); also elsewhere on the board
VCC: C5.1 (+), C9.1 (+), C10.1 (+), C11.1 (+), C12.1 (+), C13.1 (+), C14.1 (+), C15.1 (+), C16.1 (+), C17.1 (+), C20.1 (+), C32.1, J3.A3 (+5), U7.3 (+VOUT), U12.3 (INPUT); also elsewhere on the board
WAIT: J3.B21 (WAIT); also elsewhere on the board
WR: J3.B19 (WR); also elsewhere on the board
